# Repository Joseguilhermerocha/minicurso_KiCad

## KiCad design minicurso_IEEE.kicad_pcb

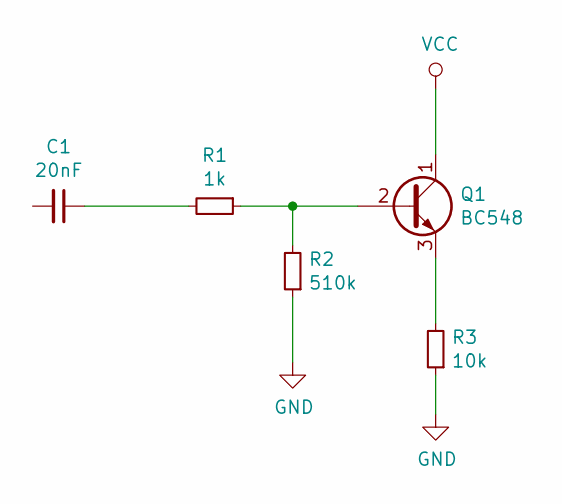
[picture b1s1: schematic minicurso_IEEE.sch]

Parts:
C1: 20nF; C_Disc_D3.0mm_W2.0mm_P2.50mm
Q1: BC548; TO-92_Inline
R1: 1k; R_Axial_DIN0204_L3.6mm_D1.6mm_P7.62mm_Horizontal
R2: 510k; R_Axial_DIN0204_L3.6mm_D1.6mm_P7.62mm_Horizontal
R3: 10k; R_Axial_DIN0204_L3.6mm_D1.6mm_P7.62mm_Horizontal

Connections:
GND: R2.1, R3.1
unnamed: C1.1, R1.2
unnamed: Q1.2 (B), R1.1, R2.2
unnamed: Q1.3 (E), R3.2
VCC: Q1.1 (C)

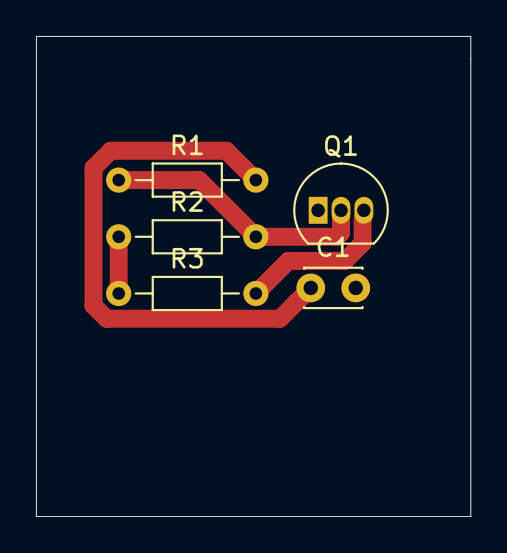
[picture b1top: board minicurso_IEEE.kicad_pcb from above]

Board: 2 copper layers, 24.1 x 26.7 mm, 5 parts (0 on the bottom side), 4 nets.

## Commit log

2019-08-09 Esquemático da primeira parte
    O amplificador de guitarra teve seu esquemático dividido em três partes. Está é a primeira.
2019-08-10 Parte-1 footprints
    Foi adicionado os footprints dos componentes da primeira parte do projeto
2019-08-10 Adicionado os furos e marcações da placa
    Foi feita as linhas e foi gerado os arquivos de marcações e furos da placa :D
